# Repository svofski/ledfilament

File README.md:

# ledfilament
ATtiny12L 75V LED Filaments driver

These are flexible LED filaments, of which I learned from [this video](http://www.youtube.com/watch?v=H_XiunR-cAQ)
by [mikeselectricstuf](http://www.electricstuff.co.uk/) 
They require around 75V to light up, so a for 
these LEDs is essentially the same as Nixie tube driver, which is awesome.

Using any serious microcontroller for this experiment would be wasteful. Fortunately, I had
an ATtiny12L salvaged from an ink cartridge. Unfortunately, avr-gcc would not even
generate code for it. Fortunately, its task is so simple that it wasn't a trouble at all
to code it in assembly.

This is a boost converter. R2 is a bleed resistor that does not let the MOSFET to stay open 
when the micro is being programmed. The inductor value is anything around 100uH. The 
feedback loop to keep the voltage at set value is implemented using resistor divider
`RV1-R3` and the builtin comparator of ATtiny12L. 

It was also an experiment with homemade UV soldermask. I did not get it at first attempt, 
but it worked out nicely after a few attempts. As usual with UV curable things, the trick 
is to have opaque zones in the transparency really opaque.

-----
2015 Viacheslav Slavinsky https://www.sensi.org/~svo

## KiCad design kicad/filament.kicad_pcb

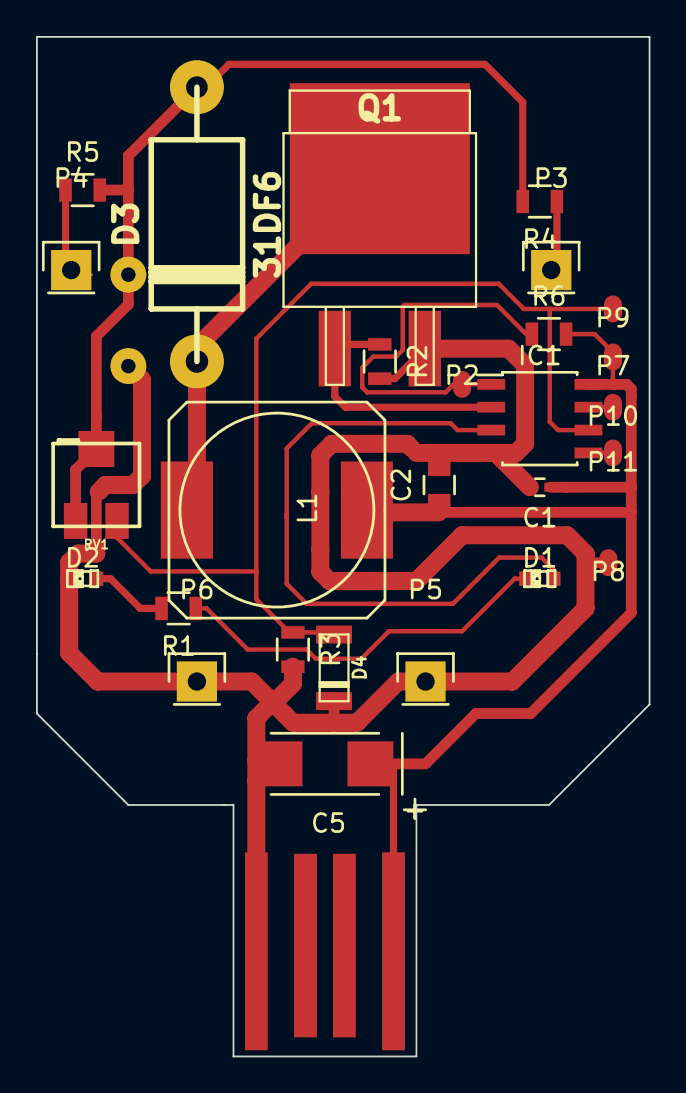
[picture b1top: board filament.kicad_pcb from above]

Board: 2 copper layers, 34.0 x 56.6 mm, 29 parts (1 on the bottom side), 14 nets.

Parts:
C1: 0.1; C_0402
C2: 0.33; C_0805
C3: 4,7uF/300V; Elko_vert_20x10mm_RM5
C5: 220uF; TantalC_SizeC_EIA-6032_Reflow
D1, D2: Led_Small; LED-0603
D3: 31DF6; diode_do201
D4: BZV55-C3V3; sod80c
IC1: ATTINY12-S; SOIC-8_3.9x4.9mm_Pitch1.27mm
L1: 220uH; SELF-WE-PD-XXL
P1: USB_A; USBPCB
P2, P7, P8, P9, P10, P11: CONN_01X01; wirepad-1
P3, P4, P5, P6: CONN_01X01; Pin_Header_Straight_1x01
Q1: IRF630NS; d2-pak
R1: 68; R_0805
R2: 1M; R_0805
R3: 4K7; R_0805
R4, R5: 510; R_0805
R6: 10K; R_0805
RV1: 500K; trim_bourns_3214j

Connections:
+5V: C1.1, C2.1, C5.1, IC1.8, L1.1, P1.1, P7.1, R6.2
GND: C1.2, C2.2, C3.2, C5.2, D2.1, D4.2, IC1.4, P1.4, P5.1, P6.1, P8.1, Q1.3, R2.2, R3.2
unnamed: C3.1, D3.1, R4.2, R5.2, RV1.1, RV1.2
unnamed: D1.1, R1.1
unnamed: D1.2, IC1.3
unnamed: D2.2, R1.2
unnamed: D3.2, L1.2, Q1.2
unnamed: D4.1, IC1.6, P9.1, R3.1, RV1.3
unnamed: IC1.1, P2.1, R6.1
unnamed: IC1.2, Q1.1, R2.1
unnamed: IC1.5, P11.1
unnamed: IC1.7, P10.1
unnamed: P3.1, R4.1
unnamed: P4.1, R5.1

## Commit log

2015-06-14 tiny12l-based charge pump LED filament driver
2015-09-10 circuito png
